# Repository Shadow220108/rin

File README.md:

<h1 align="center">
<br>

<br>
Rin
<br>
</h1>

<h3 align="center">

A tiny USB-C to UART converter

</h3>

<div align="center">

</div>

Rin is a small USB to UART board. You plug it into your laptop with a USB-C cable and use it to talk to microcontrollers over serial, so you can flash a board or read its serial monitor. There are two versions of it, v1 uses the Microchip MCP2200 and v2 uses the CH340C and can also flash an ESP32 without you pressing any buttons.

The whole design process is in [JOURNAL.md](JOURNAL.md), around 38 hours for both versions.

## Rin v2 (CH340C)

v2 is the one I would actually use. It's 38 x 25 mm, smaller than v1, and it has some stuff v1 was missing. There's a 500mA polyfuse on VBUS so if the board on the other side shorts, my laptop's USB port is safe, and a USBLC6 ESD chip on D+ and D- so static doesn't kill the CH340C. The CH340C has its own oscillator so there's no crystal anymore.

The 5V / 3.3V jumper from v1 is now a slide switch, cause I kept losing the jumper cap. The AP2112K regulator gives 600mA, which is enough to run an ESP32 straight from the header.

The best part is the ESP32 auto reset. Two MMBT3904 transistors sit on DTR and RTS, and when you hit upload, esptool pulls EN and IO0 low by itself and the ESP32 goes into flashing mode. No more holding the boot button and pressing reset every time!!

The pin names are printed right on the silkscreen so you don't have to keep checking this readme.

J2 is the standard FTDI pinout so it plugs straight into stuff like an Arduino Pro Mini. For an ESP32, connect TX to RX, RX to TX, GND to GND, and EN and IO0 from J3.

| Schematic |
| --- |
|  |

| PCB | Back |
| --- | --- |
|  |  |

## Rin v1 (MCP2200)

<div align="center">

</div>

v1 was my first USB chip board. It's 40 x 30 mm with a black solder mask, the Rin logo and a Hack Club flag on the front, and "made with love by shadow" on the back. It runs off a 12MHz crystal, has a jumper to pick 3.3V or 5V logic, red and green LEDs that blink when data goes through and a blue power LED. The MCP2200 also has 6 free GPIOs, so I put them on the headers next to the UART pins.

| Schematic | PCB |
| --- | --- |
|  |  |

## Why was it made?

Every time I wanted to use serial I had to borrow a USB to UART from someone or use the old one from the lab that works half the time. So I made my own! And then I made it again but smaller and with auto reset, cause I flash ESP32s a lot :D

## BOM

v1 cost (JLCPCB)

| Component | Qty | Price | Vendor |
| --- | --- | --- | --- |
| PCB | 5 (MOQ) | 2$ | JLCPCB |
| PCBA | 2 (MOQ) | 23.16$ | JLCPCB |
| Shipping | | 8.93$ | |
| Total | | 34.09$ | |

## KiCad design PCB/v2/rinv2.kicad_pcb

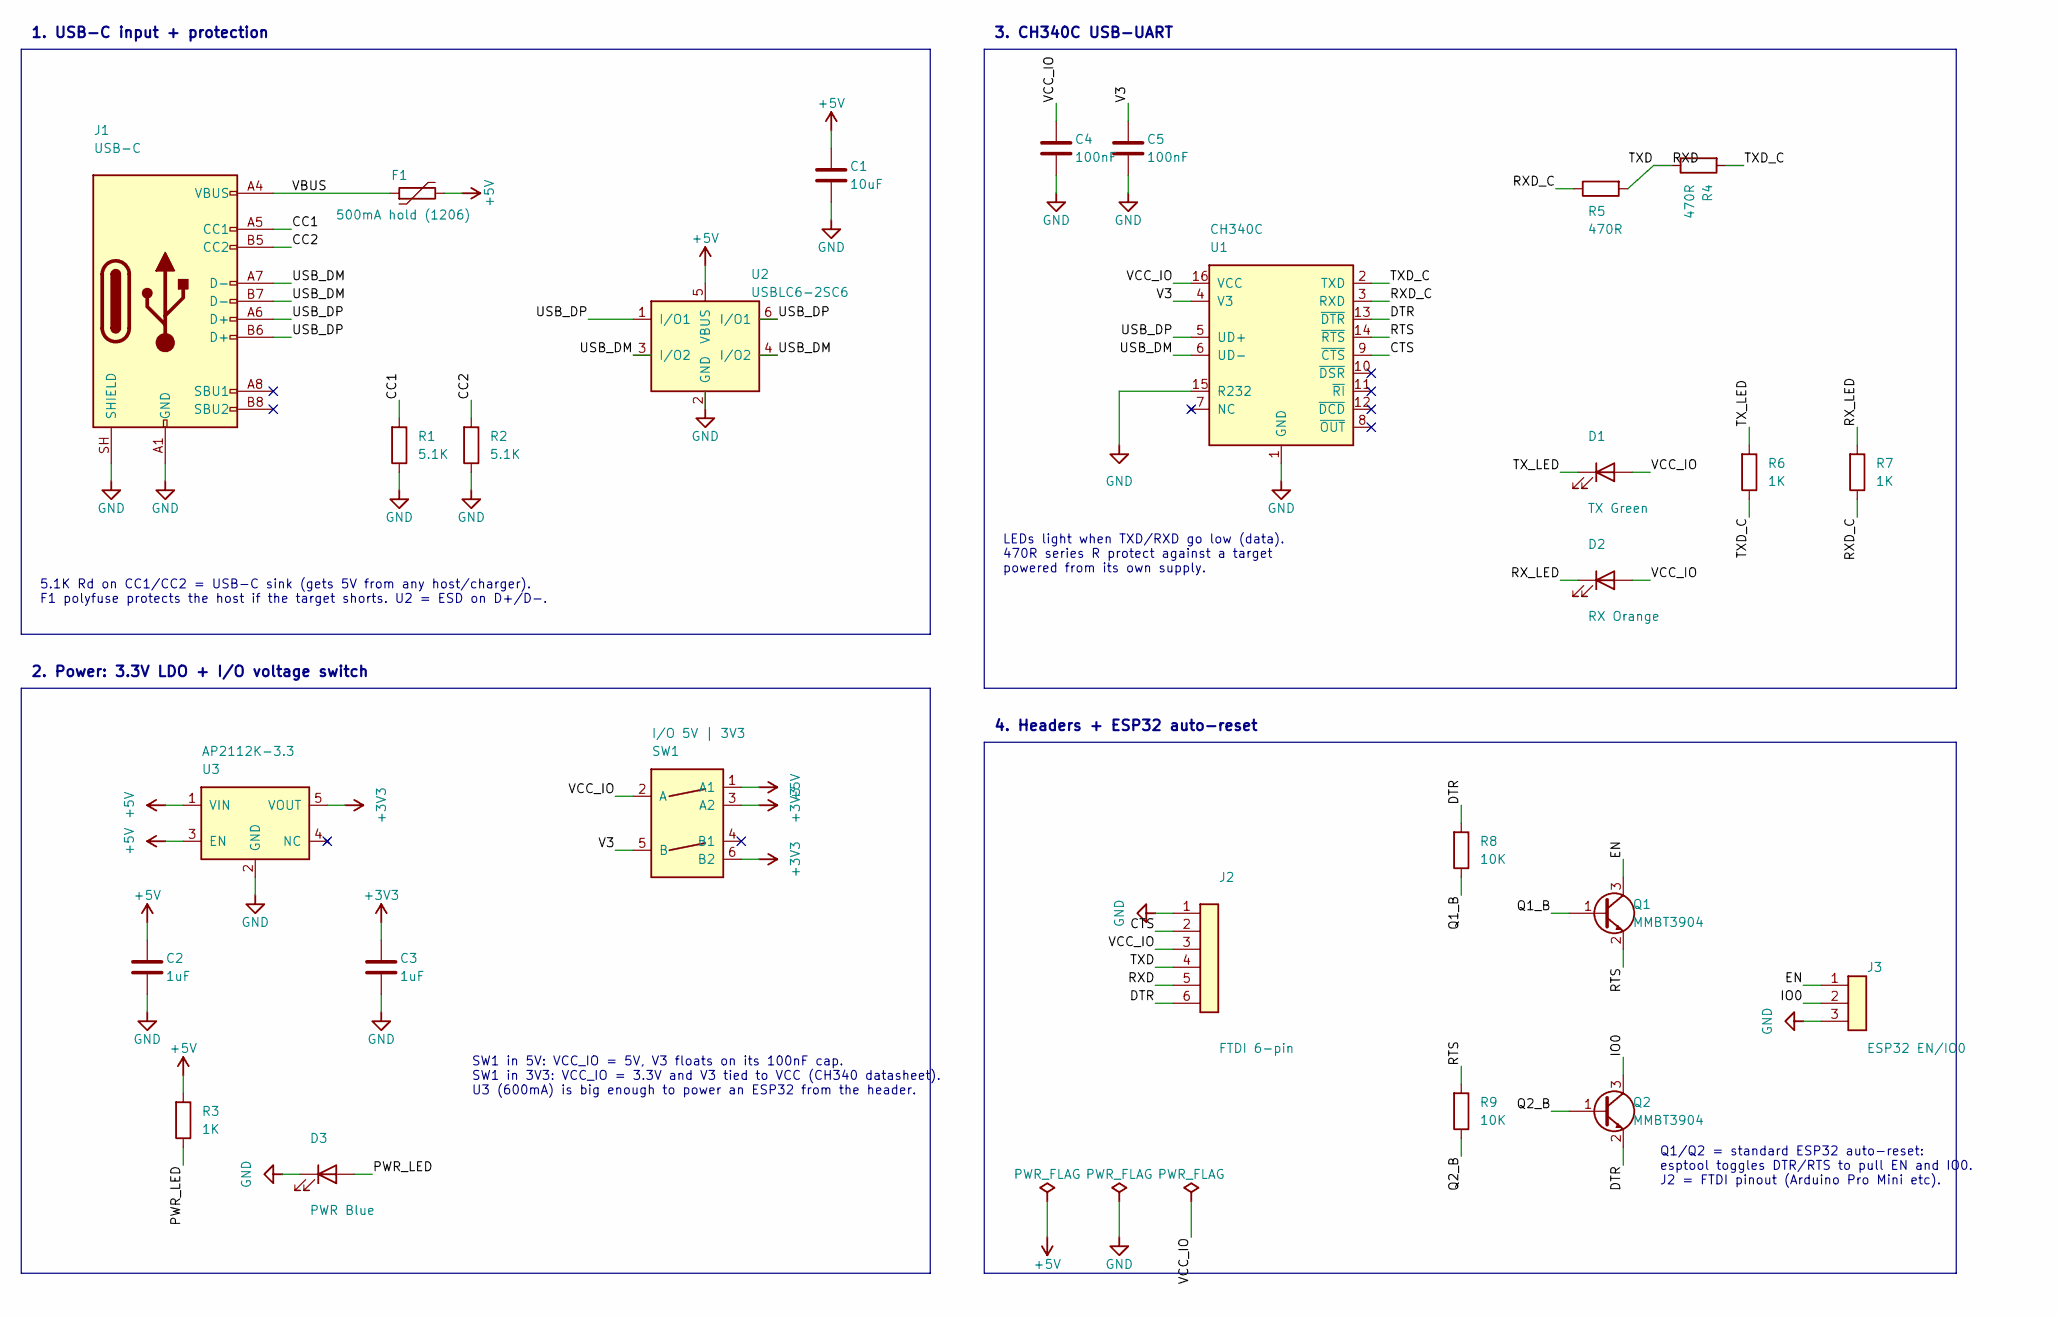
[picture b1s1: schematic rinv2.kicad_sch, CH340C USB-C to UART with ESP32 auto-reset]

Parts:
C1: 10uF; C_0603_1608Metric
C2, C3: 1uF; C_0402_1005Metric
C4, C5: 100nF; C_0402_1005Metric
D1: TX Green; LED_0603_1608Metric
D2: RX Orange; LED_0603_1608Metric
D3: PWR Blue; LED_0603_1608Metric
F1: 500mA hold (1206); Fuse_1206_3216Metric
J1: USB-C; USB_C_Receptacle_HRO_TYPE-C-31-M-12
J2: FTDI 6-pin; PinHeader_1x06_P2.54mm_Vertical
J3: ESP32 EN/IO0; PinHeader_1x03_P2.54mm_Vertical
Q1, Q2: MMBT3904; SOT-23
R1, R2: 5.1K; R_0402_1005Metric
R3, R6, R7: 1K; R_0402_1005Metric
R4, R5: 470R; R_0402_1005Metric
R8, R9: 10K; R_0402_1005Metric
SW1: I/O 5V | 3V3; SW_DPDT_CK_JS202011JCQN
U1: CH340C; SOIC-16_3.9x9.9mm_P1.27mm
U2: USBLC6-2SC6; SOT-23-6
U3: AP2112K-3.3; SOT-23-5

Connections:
+3V3: C3.1, SW1.3 (A2), SW1.6 (B2), U3.5 (VOUT)
+5V: C1.1, C2.1, F1.2, R3.1, SW1.1 (A1), U2.5 (VBUS), U3.1 (VIN), U3.3 (EN)
CC1: J1.A5 (CC1), R1.1
CC2: J1.B5 (CC2), R2.1
CTS: J2.2, U1.9 (~CTS)
DTR: J2.6, Q2.2 (E), R8.1, U1.13 (~DTR)
EN: J3.1, Q1.3 (C)
GND: C1.2, C2.2, C3.2, C4.2, C5.2, D3.1 (K), J1.A1 (GND), J1.A12 (GND), J1.B1 (GND), J1.B12 (GND), J1.SH (SHIELD), J2.1, J3.3, R1.2, R2.2, U1.1 (GND), U1.15 (R232), U2.2 (GND), U3.2 (GND)
IO0: J3.2, Q2.3 (C)
PWR_LED: D3.2 (A), R3.2
Q1_B: Q1.1 (B), R8.2
Q2_B: Q2.1 (B), R9.2
RTS: Q1.2 (E), R9.1, U1.14 (~RTS)
RXD_C: R5.2, R7.2, U1.3 (RXD)
RX_LED: D2.1 (K), R7.1
TXD_C: R4.1, R6.2, U1.2 (TXD)
TX_LED: D1.1 (K), R6.1
USB_DM: J1.A7 (D-), J1.B7 (D-), U1.6 (UD-), U2.3 (I/O2), U2.4 (I/O2)
USB_DP: J1.A6 (D+), J1.B6 (D+), U1.5 (UD+), U2.1 (I/O1), U2.6 (I/O1)
V3: C5.1, SW1.5 (B), U1.4 (V3)
VBUS: F1.1, J1.A4 (VBUS), J1.A9 (VBUS), J1.B4 (VBUS), J1.B9 (VBUS)
VCC_IO: C4.1, D1.2 (A), D2.2 (A), J2.3, SW1.2 (A), U1.16 (VCC)

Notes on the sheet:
3. CH340C USB-UART
5.1K Rd on CC1/CC2 = USB-C sink (gets 5V from any host/charger). F1 polyfuse protects the host if the target shorts. U2 = ESD on D+/D-.
1. USB-C input + protection
Q1/Q2 = standard ESP32 auto-reset: esptool toggles DTR/RTS to pull EN and IO0. J2 = FTDI pinout (Arduino Pro Mini etc).
LEDs light when TXD/RXD go low (data). 470R series R protect against a target powered from its own supply.
2. Power: 3.3V LDO + I/O voltage switch
SW1 in 5V: VCC_IO = 5V, V3 floats on its 100nF cap. SW1 in 3V3: VCC_IO = 3.3V and V3 tied to VCC (CH340 datasheet). U3 (600mA) is big enough to power an ESP32 from the header.
4. Headers + ESP32 auto-reset

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
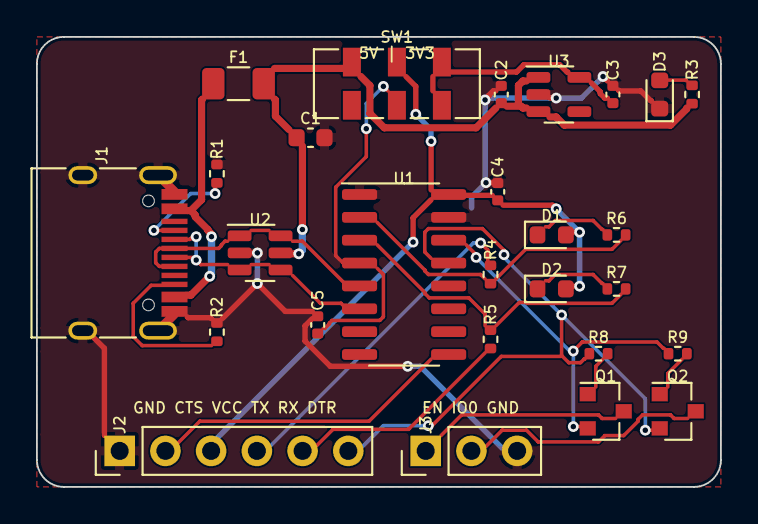
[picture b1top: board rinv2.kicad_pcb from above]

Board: 2 copper layers, 38.0 x 25.0 mm, 27 parts (0 on the bottom side), 24 nets.

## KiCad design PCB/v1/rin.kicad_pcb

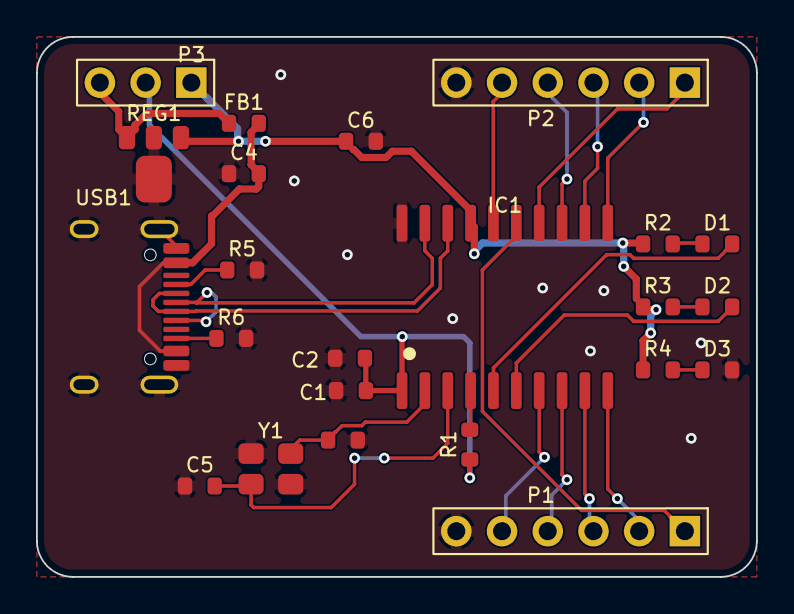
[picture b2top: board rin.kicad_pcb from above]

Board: 2 copper layers, 40.0 x 30.0 mm, 23 parts (0 on the bottom side), 27 nets.

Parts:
C1: 2.2uF; C_0603_1608Metric
C2: 100nF; C_0603_1608Metric
C3, C5: 22pF; C_0603_1608Metric
C4: 4.7uF; C_0603_1608Metric
C6: 330nF; C_0603_1608Metric
D1: RX-RED; LED_0603_1608Metric
D2: TX-GREEN; LED_0603_1608Metric
D3: Power-Blue; LED_0603_1608Metric
FB1: FerriteBead; L_0603_1608Metric
IC1: MCP2200-I_SO; SOIC-20W_7.5x12.8mm_P1.27mm
P1, P2: Header 6; PinHeader_1x06_P2.54mm_Vertical
P3: Header 3; PinHeader_1x03_P2.54mm_Vertical
R1: 4.7K; R_0603_1608Metric
R2, R3, R4: 470R; R_0603_1608Metric
R5, R6: 5.1K; R_0603_1608Metric
REG1: RT9166-33GX; SOT-89-3
USB1: USB-C (HRO TYPE-C-31-M-12); USB_C_Receptacle_HRO_TYPE-C-31-M-12
Y1: 12MHz; Crystal_SMD_3225-4Pin_3.2x2.5mm

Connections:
+5VUSB: FB1.1, P3.3, REG1.3
CC1: R5.1, USB1.A5
CC2: R6.1, USB1.B5
CTS: IC1.13, P2.4
D+: IC1.19, USB1.A6, USB1.B6
D-: IC1.18, USB1.A7, USB1.B7
GND: C1.2, C2.2, C3.2, C4.2, C5.2, C6.2, D3.1, IC1.20, P1.6, P2.6, R5.2, R6.2, REG1.2, USB1.A1, USB1.A12, USB1.B1, USB1.B12, USB1.S1, Y1.2, Y1.4
GP0: IC1.16, P2.5
GP1: IC1.15, P1.1
GP2: IC1.14, P2.1
GP3: IC1.9, P1.3
GP4: IC1.8, P1.4
GP5: IC1.7, P1.5
LED_B: D3.2, R4.2
LED_G: D2.2, R3.2
LED_R: D1.2, R2.2
OSC1: C3.1, IC1.2, Y1.3
OSC2: C5.1, IC1.3, Y1.1
RST: IC1.4, R1.2
RTS: IC1.11, P2.2
RX: IC1.10, P1.2
RXLED: D2.1, IC1.6
TX: IC1.12, P2.3
TXLED: D1.1, IC1.5
VBUS_F: C4.1, FB1.2, USB1.A4, USB1.A9, USB1.B4, USB1.B9
VCC: C1.1, C2.1, IC1.1, P3.2, R1.1
VUSB: C6.1, IC1.17, P3.1, R2.1, R3.1, R4.1, REG1.1
